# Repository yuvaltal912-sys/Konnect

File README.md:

<div align="center">

# Konnect is MOVING!!!

</div>

> ## Konnect has moved to Konnect-EDA
>
> **This repository will be archived at midnight (US Eastern) at the end of Sunday, October 25, 2026.**
> After that it's read-only. Everything here stays readable, and the releases already published stay
> available under the AGPL-3.0, but no new issues, comments or pull requests can be added.
>
> Konnect continues as **[Konnect-EDA](https://github.com/Orchis-ai-LLC/Konnect-EDA)**, from
> Orchis.ai LLC. It's the same AI-assisted KiCad design tool, and all development continues there:
>
> - **Downloads:** the [Konnect-EDA Releases page](https://github.com/Orchis-ai-LLC/Konnect-EDA/releases);
>   the first release is coming soon. Konnect-EDA is commercial, closed-source software, **free to use
>   during the beta** (until version 1.0).
> - **Bugs and feature requests:** the
>   [Konnect-EDA issue tracker](https://github.com/Orchis-ai-LLC/Konnect-EDA/issues).
> - **Want to help build it?** Sign up to contribute at
>   **[orchis.ai/konnect/join](https://orchis.ai/konnect/join)**.
> - **Contributed to Konnect?** Please answer your sign-off email, or sign in with GitHub at
>   [orchis.ai/konnect/sign-off](https://orchis.ai/konnect/sign-off). It's open until November 20.
>
> Thank you to everyone who built Konnect with us.

> **Status: beta.** The core toolchain is tested and working, but this is a young
> release and it wants real-world mileage and review. Issues and PRs are welcome —
> see [CONTRIBUTING.md](CONTRIBUTING.md) and the
> [naming conventions](docs/NAMING_CONVENTIONS.md).

> ## Add realtime research to KiCAD MCP and Konnect. Introducing Nimrod
>
> [**Nimrod**](https://nimrod.orchis.ai) is our web-research MCP server:
> quality-scored Google search, clean webpage extraction, and deep multi-source
> research. Design the board with Konnect while Nimrod pulls live parts availability, datasheets,
> and errata — no more guessing from year-old training data
>
> - Works with claude.ai, Claude Desktop, Claude Code, VS Code, and any MCP client
> - 1 credit = 1 search · extraction always free · free 50-credit trial, no card
> - Official MCP Registry: [`ai.orchis/nimrod`](https://registry.modelcontextprotocol.io)

**AI-assisted PCB design for KiCAD 10.** Konnect is a native KiCAD plugin — a single
Rust binary — that lets Claude and other AI assistants design schematics and PCBs
through the [Model Context Protocol](https://modelcontextprotocol.io) (MCP).

**269 tools across 22 on-demand toolsets.** Schematic capture, PCB layout and
routing, ERC/DRC, design-review audits, JLCPCB part search, reference
circuits, and a full manufacturing export pipeline — with bundled skills and agents
that teach Claude KiCAD conventions out of the box.

## Why Konnect exists

Konnect is the successor to [KiCAD-MCP-Server](https://github.com/mixelpixx/KiCAD-MCP-Server),
a Python/TypeScript project that proved AI-driven PCB design works — and, in the
process, showed exactly where that architecture runs out of road. Konnect was built
to fix those specific problems:

**The call path was too long.** In the original server, a single tool call travels
through TypeScript, schema validation, a spawned Python subprocess, JSON over
stdin/stdout, a command router, and finally SWIG-generated C++ proxy objects before
anything touches your board. That's four language and serialization boundaries, each
with its own failure modes — subprocess lifecycle management, stdout parsing that
filters out warnings KiCAD leaks into the stream, chunked-JSON reassembly. In
Konnect, a tool call is a function call. One process, one language, no plumbing.

**The dependency surface was enormous.** Running the original means carrying Node.js
and its npm tree, Python and its pip packages, wxPython, kicad-skip, and KiCAD's
SWIG bindings — two package ecosystems plus a binding layer, every one of them a
moving target that can break an install. Konnect is a single static binary —
20–25 MB depending on platform, a ~9 MB download. There is nothing to install
alongside it and nothing to version-match.

**SWIG is a dead end.** The original's PCB backend depends on KiCAD's SWIG Python
bindings, which KiCAD is deprecating in favor of its IPC API. SWIG also carried
real operational scars: a zone-fill call that can segfault the backend, proxy-object
comparison bugs, and a fallback path that can silently swap backends mid-session.
Konnect talks to KiCAD 10 through the official IPC API (protobuf over NNG) — the
interface KiCAD is investing in — with real-time board edits that integrate with
KiCAD's own undo/redo.

**Schematic edits should not corrupt files.** Konnect edits `.kicad_sch` files
through its own S-expression engine with atomic writes (write, fsync, rename), UUID
preservation, and round-trip tests — no third-party schematic library with known
gaps, no text-manipulation workarounds.

**Context economy is a feature.** Exposing all 269 tools to an LLM costs roughly 23K
tokens of context on every listing. Konnect's router loads a starter kit (~2K
tokens) and lets the model pull in toolsets on demand — plus built-in observability
(`get_recent_calls`, `server_stats`, JSONL call logs) so the model can diagnose its
own tool failures.

The result is smaller, faster to install, aligned with where KiCAD is going, and
built for production use rather than experimentation. The original project remains
open, maintained, and useful — see [the comparison below](#relationship-to-kicad-mcp-server).

## What it does

Instead of describing changes and applying them by hand, the AI works your project
directly:

- **Place and wire schematic components** — add resistors, ICs, connectors; wire them
  together by pin name
- **Lay out the PCB** — place, move, rotate, and route footprints in real time via
  KiCAD's IPC API, with full undo/redo integration
- **Run design checks** — ERC, DRC, connectivity validation, decoupling audits,
  power-rail review, BOM health checks
- **Export production files** — Gerbers, drill, BOM, pick-and-place, 3D models, PDF
- **Search JLCPCB parts** — find in-stock components in a local 2.5M-part catalog and
  suggest alternatives
- **Start from reference circuits** — USB-C, LDO, buck converter, STM32, I2C, LED
  templates with verified component values
- **Watch it happen** — a live schematic viewer auto-refreshes as the AI edits

The full tool catalog is documented in [tool-directory.md](tool-directory.md).

## How it works

| Layer | Mechanism |
|-------|-----------|
| Schematic editing | Direct `.kicad_sch` S-expression editing with atomic writes (no KiCAD required) |
| PCB editing | KiCad 10 IPC API (NNG + protobuf) — real-time and undo-aware; single-footprint placement has a safe headless fallback |
| Specctra routing | Revision-bound Rust DSN export, local Freerouting MCP routing, and strict one-transaction SES import; an authenticated KiCad 10 native-export bridge is explicit opt-in |
| Exports & checks | `kicad-cli` subprocess (Gerber, PDF, ERC, DRC, …) |
| Transport | MCP JSON-RPC over stdio (default), or Streamable HTTP (`transport = "http"` / `"both"`) |

Explore the request path and safety boundaries in the
[interactive architecture diagrams](docs/ARCHITECTURE_DIAGRAMS.md). They are
published from a standalone documentation repository and add no dependencies to
Konnect.

## Installation

### From the KiCAD Plugin Manager (recommended)

1. Download the package for your OS from [Releases](https://github.com/mixelpixx/Konnect/releases):
   `konnect-pcm-v<version>-windows.zip`, `-macos.zip`, or `-linux.zip`. Each
   bundles that platform's server binary — the macOS package is a universal
   build, so one download covers Apple Silicon and Intel. (The `konnect-pcm-*`
   assets are the KiCAD plugin packages; the other archives are standalone
   server binaries.)
2. Open KiCAD 10 → **Plugin and Content Manager**
3. Click **Install from File** and select the zip
4. Restart KiCAD

Verify: open the **PCB Editor** → **Tools → External Plugins** → you should see
**Konnect**.

For KiCad 10, the Konnect settings dialog also offers an optional **native
Specctra bridge**. When enabled, `export_specctra_dsn` can ask the active PCB
Editor to generate its native DSN while Konnect still binds the export to the
exact IPC snapshot and creates the strict reverse manifest used during SES
import. The bridge is local-only, authenticated, disabled by default, and not
the KiCad 11 integration path. Konnect uses its Rust exporter by default;
`native_bridge_mode: "prefer"` enables fallback to Rust when the bridge is
unavailable, while `"require"` refuses instead.

For end-to-end autorouting, run `check_freerouting`, then
`export_specctra_dsn` → `route_specctra_dsn` →
`plan_specctra_ses_import` / `apply_specctra_ses`. Readiness reports engine
discovery, native-MCP compatibility, and complete bridge availability
separately. The owned Java child is loopback-only and is reaped on success,
failure, timeout, or cancellation. The first supported profile preserves fixed
straight tracks and through vias; unlocked routing, arcs, zones, and unsupported
geometry are rejected before mutation.

### Build from source

```bash
# protoc is required (protobuf code generation), and cmake (the nng crate
# compiles the NNG C library with it).
# Windows: choco install protoc cmake
# macOS:   brew install protobuf cmake
# Linux:   apt install protobuf-compiler cmake
cargo build --release -p konnect
```

### Install guidance for your AI client

Konnect bundles shared KiCad skills for Claude and Codex. Select the client when
installing, checking, or removing that guidance:

```bash
# Existing behavior remains the default: Claude skills, agents, and hooks
konnect init

# Codex installs only the shared skills under ~/.agents/skills
konnect init --client codex
konnect status --client codex
konnect uninstall --client codex
```

MCP server startup never installs or restores guidance. Run `konnect init`
explicitly when you want those files installed; after `konnect uninstall`,
starting the server leaves them removed.

Guidance written by an older `konnect init` is not updated by upgrading the
binary. `konnect status` compares every installed skill, agent, and hook with
the bundle in the binary you run and marks each `current`, `different`, or
`missing`. The server makes the same check once for each installed version:
the first start after `konnect init` compares the files, records
the result in `~/.konnect`, and adds a one-line notice to its `initialize`
instructions if guidance is out of sync. Later starts reuse that record, so
guidance you chose to keep is not reported again. `get_installation_info`
shows the result. Re-run `konnect init` to update it.
It overwrites differing files, so keep a copy of any file you edited. `--client` remains accepted in server
commands for compatibility. For example, register a standalone binary with the
Codex CLI using:

```bash
codex mcp add konnect -- /path/to/konnect --client codex
```

Claude remains the default when `--client` is omitted. The installer tracks the
two clients independently, and a Codex install does not create or modify
`~/.claude`.

`--help` on any subcommand prints that subcommand's usage and writes nothing —
`konnect init --help` describes the installer rather than running it. An
argument Konnect does not recognise is an error rather than being ignored, so a
typo such as `--cleint codex` stops instead of quietly installing for the
default client.

To verify which Konnect process an MCP client is actually using, call the
always-visible `get_installation_info` tool. It reports the serving build,
executable path, verified installation source when one can be proven, KiCad
CLI and IPC detection, and restart guidance. A missing build commit or an
`unknown` installation source means the available evidence was insufficient;
it is not silently guessed from a directory name.

### macOS

The [Releases](https://github.com/mixelpixx/Konnect/releases) page ships
standalone server binaries for both Apple Silicon (`aarch64-apple-darwin`) and
Intel (`x86_64-apple-darwin`). They are not yet code-signed, so if you download
one through a browser, clear the quarantine flag before first launch:

```bash
tar xzf konnect-v*-aarch64-apple-darwin.tar.gz
xattr -d com.apple.quarantine ./konnect   # only needed for browser downloads
./konnect --help
```

Or build from source as above (verified on Apple Silicon; the same
`target/release/konnect` binary is the MCP server).

KiCad on macOS keeps its tools inside the app bundle and they are not on
`PATH`, so point Konnect at them in `~/Library/Application Support/konnect/config.toml`:

```toml
kicad_cli = "/Applications/KiCad/KiCad.app/Contents/MacOS/kicad-cli"
kicad_binary = "/Applications/KiCad/KiCad.app/Contents/MacOS/kicad"
# KiCad 10's IPC socket on macOS (enable it in KiCad:
# Preferences → Plugins → "Enable KiCad API")
ipc_address = "ipc:///tmp/kicad/api.sock"
```

Claude Desktop's config lives at
`~/Library/Application Support/Claude/claude_desktop_config.json`:

```json
{
  "mcpServers": {
    "konnect": {
      "command": "/path/to/konnect"
    }
  }
}
```

For Claude Code, put the same snippet in a `.mcp.json` in your project root.

The macOS PCM package (`konnect-pcm-v<version>-macos.zip`) bundles a universal
server binary, so one download covers Apple Silicon and Intel. The schematic
viewer compiles and launches on macOS (Tauri 2 uses the system WKWebView —
WebView2 is only a Windows requirement) but hasn't had the same mileage as
the Windows build yet.

## Setup with Claude Desktop

After a PCM install, the server binary lives in your KiCAD documents folder:

```
C:\Users\<YOU>\Documents\KiCad\10.0\3rdparty\plugins\com_github_mixelpixx_konnect\bin\konnect.exe
```

Edit `%APPDATA%\Claude\claude_desktop_config.json`:

```json
{
  "mcpServers": {
    "konnect": {
      "command": "C:\\Users\\<YOU>\\Documents\\KiCad\\10.0\\3rdparty\\plugins\\com_github_mixelpixx_konnect\\bin\\konnect.exe"
    }
  }
}
```

Restart Claude Desktop and the Konnect tools appear. For Claude Code, drop the same
snippet into a `.mcp.json` in your project root (see [examples/](examples/)).

## Schematic viewer

A standalone viewer that auto-refreshes as the schematic file changes:

```bash
schematic-viewer.exe path\to\your\root_schematic.kicad_sch
```

Point it at the root sheet of a hierarchical design and every sub-sheet is rendered
too, with a depth-indented sheet selector in the toolbar. Edits saved from KiCAD (or
made by the AI through the schematic tools) re-render only the sheets that changed
and refresh the view live — rendering runs against temp-folder snapshots, so the
viewer never blocks KiCAD from saving. Pan with click-drag, zoom with the wheel,
`0` to fit, `R` to refresh, drag-and-drop to open a different file. Also launchable
by the AI via the `open_schematic_viewer` tool.

Needs the WebView2 runtime (pre-installed on Windows 10/11) and a KiCAD install for
`kicad-cli` (auto-discovered, or pass `--kicad-cli <path>`). Built separately from
the main workspace — see [DEV.md](DEV.md) for build steps.

## Requirements

- KiCAD 10 (Windows is the most-tested platform; macOS works from the release
  binaries or a source build — see the [macOS section](#macos) above. Linux
  compiles and passes tests in CI but hasn't had per-platform QA yet; both are
  tracked on the [roadmap](ROADMAP.md))
- `kicad-cli` (ships with KiCAD — used for exports, ERC, DRC)
- For most PCB tools: KiCAD running with the target board open (IPC API).
  `place_component`, `move_component`, `rotate_component`, and (on KiCAD
  10.0.6+) `flip_component` can safely fall back to a closed board file when
  IPC is unreachable. An older reachable KiCAD makes `flip_component` fail
  closed with `unsupported_capability`; it never edits the file underneath a
  live editor that cannot perform the native flip.

## License: free for the little guys

Konnect is licensed under the **[GNU AGPL-3.0](LICENSE)**.

If you're a hobbyist, student, freelancer, or open-source project: **use it freely,
no strings attached.** Design boards, ship them, sell them.

If you're a business: the AGPL requires that anything you build on or around Konnect —
including software provided over a network — be open-sourced under the same license.
If that doesn't work for you, **commercial licenses are available**: see
[COMMERCIAL.md](COMMERCIAL.md).

## Relationship to KiCAD-MCP-Server

The original [Python/TypeScript project](https://github.com/mixelpixx/KiCAD-MCP-Server)
remains fully open (MIT) and maintained. Konnect is where new development happens —
the architecture it proved, rebuilt for production:

| | KiCAD-MCP-Server | Konnect |
|---|---|---|
| Runtime | Node.js + Python + SWIG bindings | Single static binary (20–25 MB) |
| Tool call path | TS → subprocess → Python → SWIG C++ | Direct function call |
| PCB backend | SWIG (deprecated by KiCAD) + experimental IPC | KiCAD 10 IPC API |
| Schematic backend | kicad-skip + custom loaders | Native S-expression engine, atomic writes |
| Context cost | Router pattern | Load/unload toolsets + observability |
| Skills / agents | — | 7 skills + 2 agents bundled |
| License | MIT | AGPL-3.0 + commercial |

## Troubleshooting

**Plugin doesn't appear in KiCAD** — install via the Plugin and Content Manager (not
manual copy), then restart KiCAD.

**PCB tools return "KiCAD must be running with the board loaded"** — open KiCAD
with that board first; most PCB tools talk to the running PCB editor. Only an
unreachable KiCAD produces that message: if KiCAD is running and the tool
refuses anyway, the error is the tool's own reason for refusing.
`place_component`, `move_component`, `rotate_component`, and (on KiCAD
10.0.6+) `flip_component` can fall back to a closed board file when no KiCAD
process is reachable. An older, reachable KiCAD makes `flip_component` refuse
rather than silently editing the file underneath it.

See [docs/TROUBLESHOOTING.md](docs/TROUBLESHOOTING.md) for socket setup, tools
that don't appear after `load_toolset`, and transaction recovery.

**"kicad-cli not found"** — common install paths are auto-detected; set the path
explicitly in the plugin settings dialog, in a `settings.json` beside the binary,
or in a `konnect.toml` in the working directory. (A file under any other name
works only when passed with `--config`.)

## Support

- Community Discord: [join the Konnect community](https://discord.gg/NVp9RGMmDu)
  for installation help, AI-client setup, design-workflow discussion,
  contributor coordination, and live project-status updates
- Issues & feature requests: [GitHub Issues](https://github.com/mixelpixx/Konnect/issues)
- Roadmap: [ROADMAP.md](ROADMAP.md)
- Contributing: [CONTRIBUTING.md](CONTRIBUTING.md)

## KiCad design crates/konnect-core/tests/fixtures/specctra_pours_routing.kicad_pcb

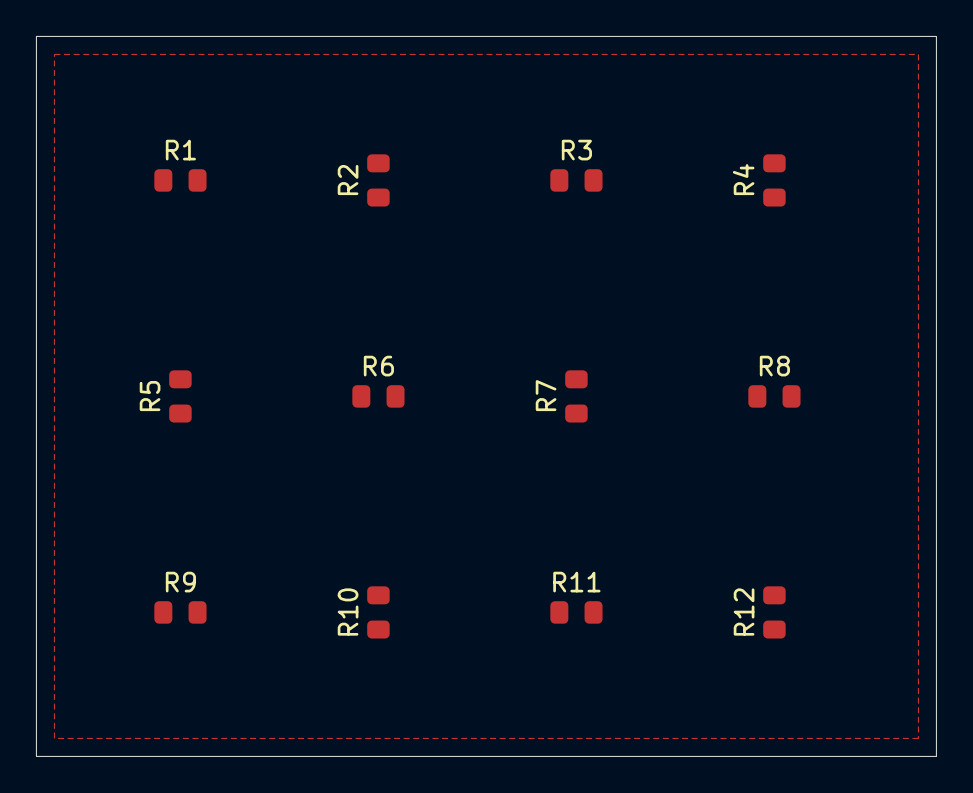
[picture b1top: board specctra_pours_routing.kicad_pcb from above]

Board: 2 copper layers, 50.0 x 40.0 mm, 12 parts (0 on the bottom side), 7 nets, no tracks yet.

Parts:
R1, R2, R3, R4, R5, R6, R7, R8, R9, R10, R11, R12: 10k; R_0805_2012Metric

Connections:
GND: R1.2, R2.2, R3.2, R4.2, R5.2, R6.2, R7.2, R8.2, R9.2, R10.2, R11.2, R12.2
S1: R1.1, R12.1
S2: R2.1, R11.1
S3: R3.1, R10.1
S4: R4.1, R9.1
S5: R5.1, R8.1
S6: R6.1, R7.1

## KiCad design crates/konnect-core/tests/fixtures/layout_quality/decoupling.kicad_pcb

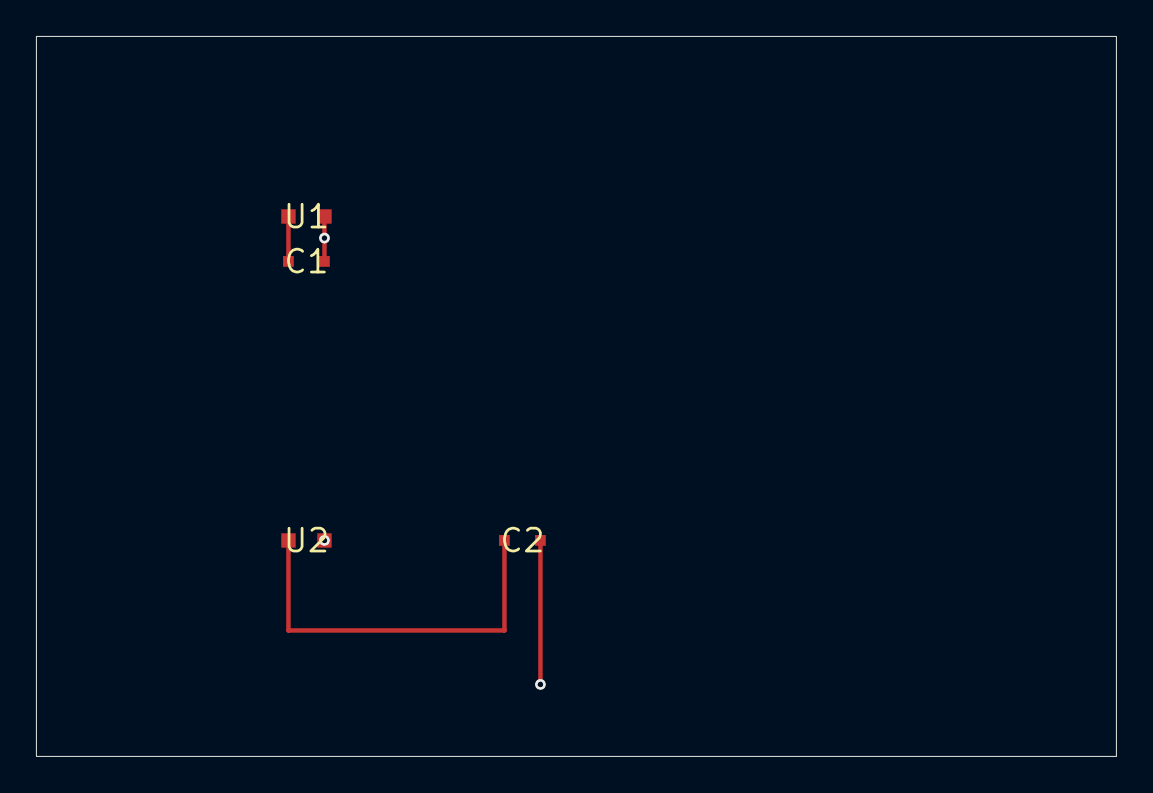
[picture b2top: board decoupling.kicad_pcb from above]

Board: 4 copper layers, 60.0 x 40.0 mm, 4 parts (0 on the bottom side), 3 nets.

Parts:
C1: C1
C2: C2
U1: U1
U2: U2

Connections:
3V3: C1.1, U1.1 (VDD)
3V3_B: C2.1, U2.1 (VDD)
GND: C1.2, C2.2, U1.2 (GND), U2.2 (GND)

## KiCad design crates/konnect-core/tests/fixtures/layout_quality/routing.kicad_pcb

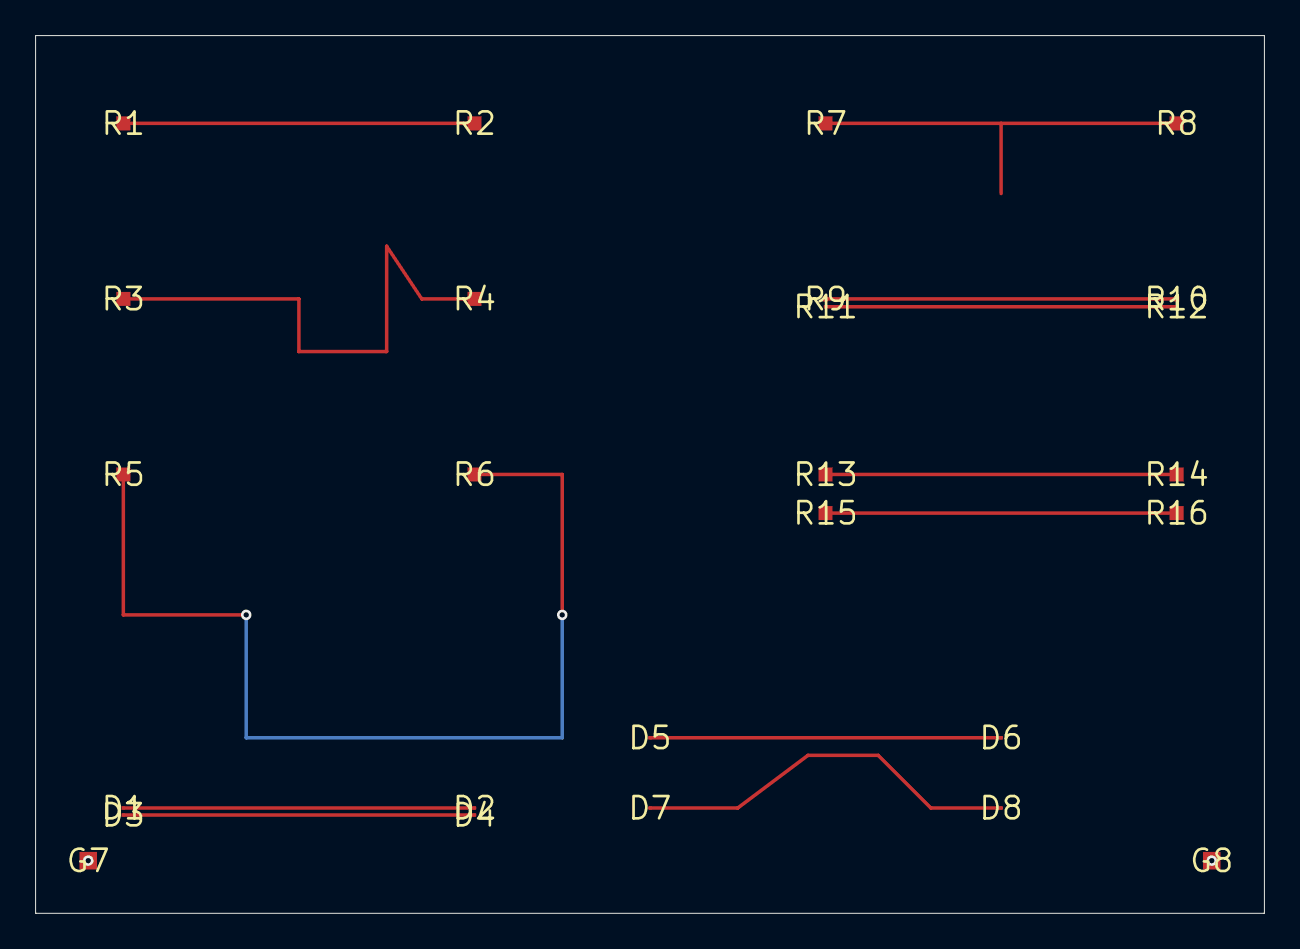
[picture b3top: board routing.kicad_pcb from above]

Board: 2 copper layers, 70.0 x 50.0 mm, 26 parts (0 on the bottom side), 13 nets.

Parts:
D1: D1
D2: D2
D3: D3
D4: D4
D5: D5
D6: D6
D7: D7
D8: D8
G7: G7
G8: G8
R1: R1
R2: R2
R3: R3
R4: R4
R5: R5
R6: R6
R7: R7
R8: R8
R9: R9
R10: R10
R11: R11
R12: R12
R13: R13
R14: R14
R15: R15
R16: R16

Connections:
DB_N: D7.1, D8.1
DB_P: D5.1, D6.1
DG_N: D3.1, D4.1
DG_P: D1.1, D2.1
GND: G7.1, G8.1
N_CLEAN: R1.1, R2.1
N_CORNER: R3.1, R4.1
N_DETOUR: R5.1, R6.1
N_PAR_A: R9.1, R10.1
N_PAR_B: R11.1, R12.1
N_SP_A: R13.1, R14.1
N_SP_B: R15.1, R16.1
N_STUB: R7.1, R8.1

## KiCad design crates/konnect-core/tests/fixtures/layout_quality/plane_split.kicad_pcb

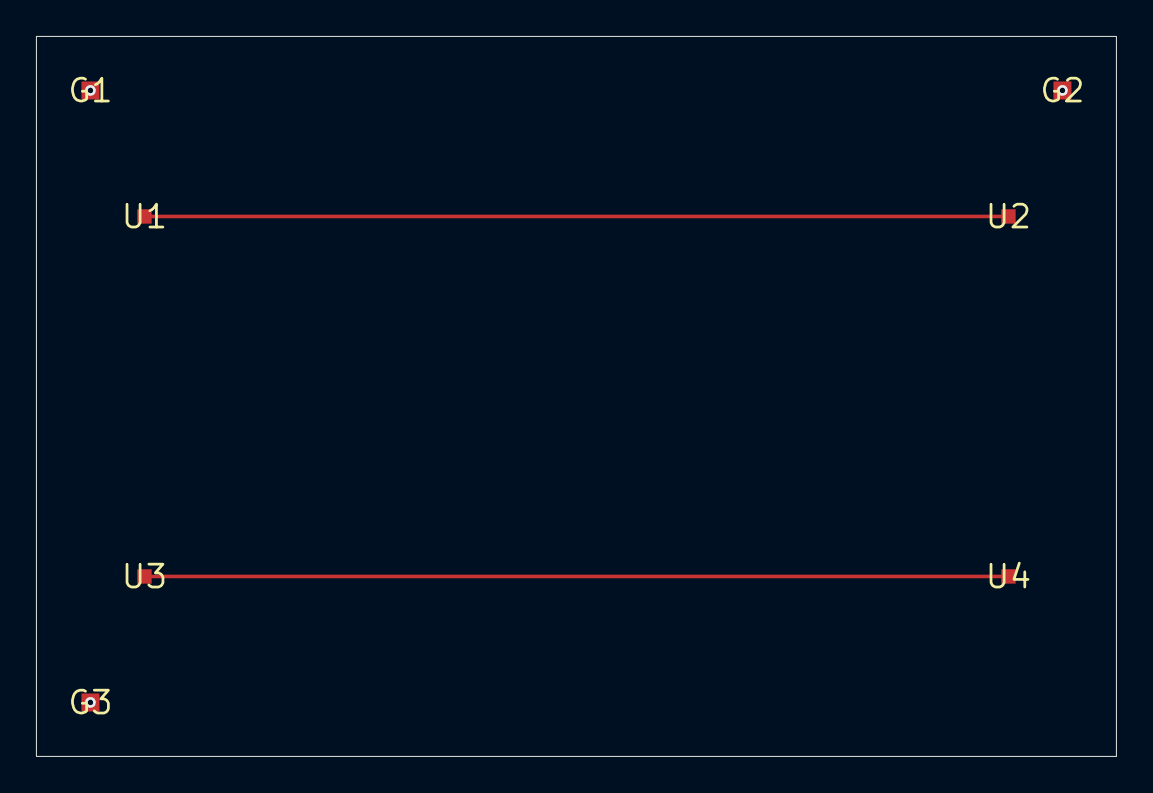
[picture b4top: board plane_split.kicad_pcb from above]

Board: 4 copper layers, 60.0 x 40.0 mm, 7 parts (0 on the bottom side), 3 nets.

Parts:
G1: G1
G2: G2
G3: G3
U1: U1
U2: U2
U3: U3
U4: U4

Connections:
CLK_OK: U1.1, U2.1
CLK_SPLIT: U3.1, U4.1
GND: G1.1, G2.1, G3.1

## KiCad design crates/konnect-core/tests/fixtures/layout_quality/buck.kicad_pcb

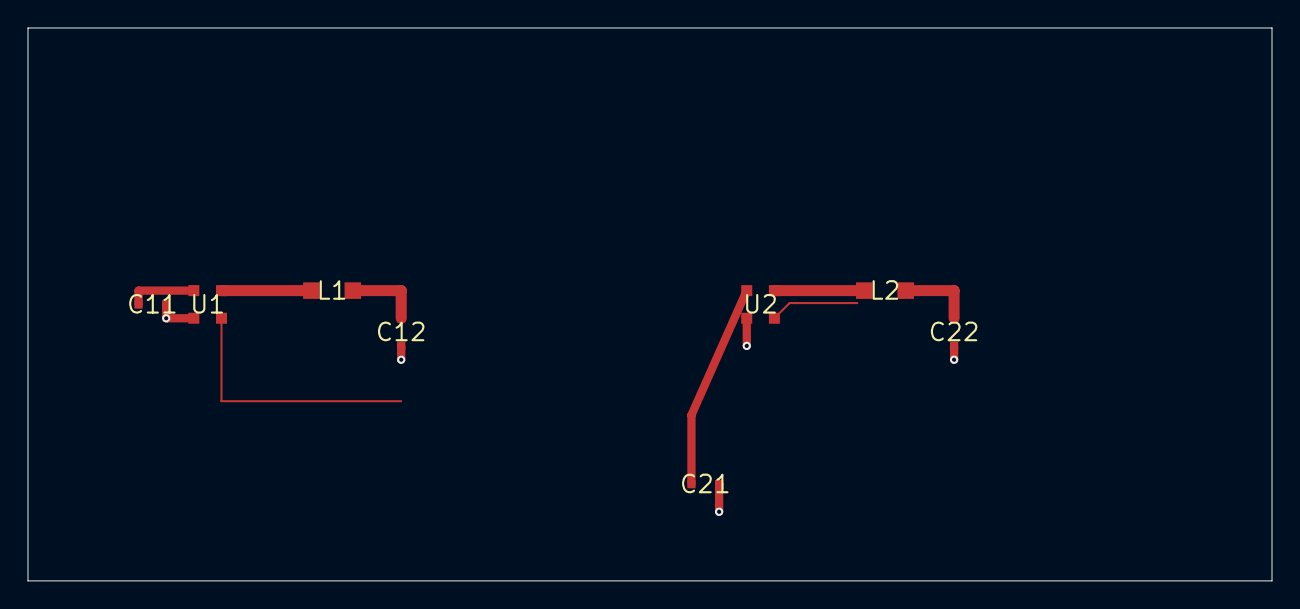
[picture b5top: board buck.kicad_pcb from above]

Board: 4 copper layers, 90.0 x 40.0 mm, 8 parts (0 on the bottom side), 7 nets.

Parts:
C11: C11
C12: C12
C21: C21
C22: C22
L1: L1
L2: L2
U1: U1
U2: U2

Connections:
GND: C11.2, C12.2, C21.2, C22.2, U1.3 (PGND), U2.3 (PGND)
SW1: L1.1, U1.2 (SW)
SW2: L2.1, U2.2 (SW)
VIN1: C11.1, U1.1 (VIN)
VIN2: C21.1, U2.1 (VIN)
VOUT1: C12.1, L1.2
VOUT2: C22.1, L2.2

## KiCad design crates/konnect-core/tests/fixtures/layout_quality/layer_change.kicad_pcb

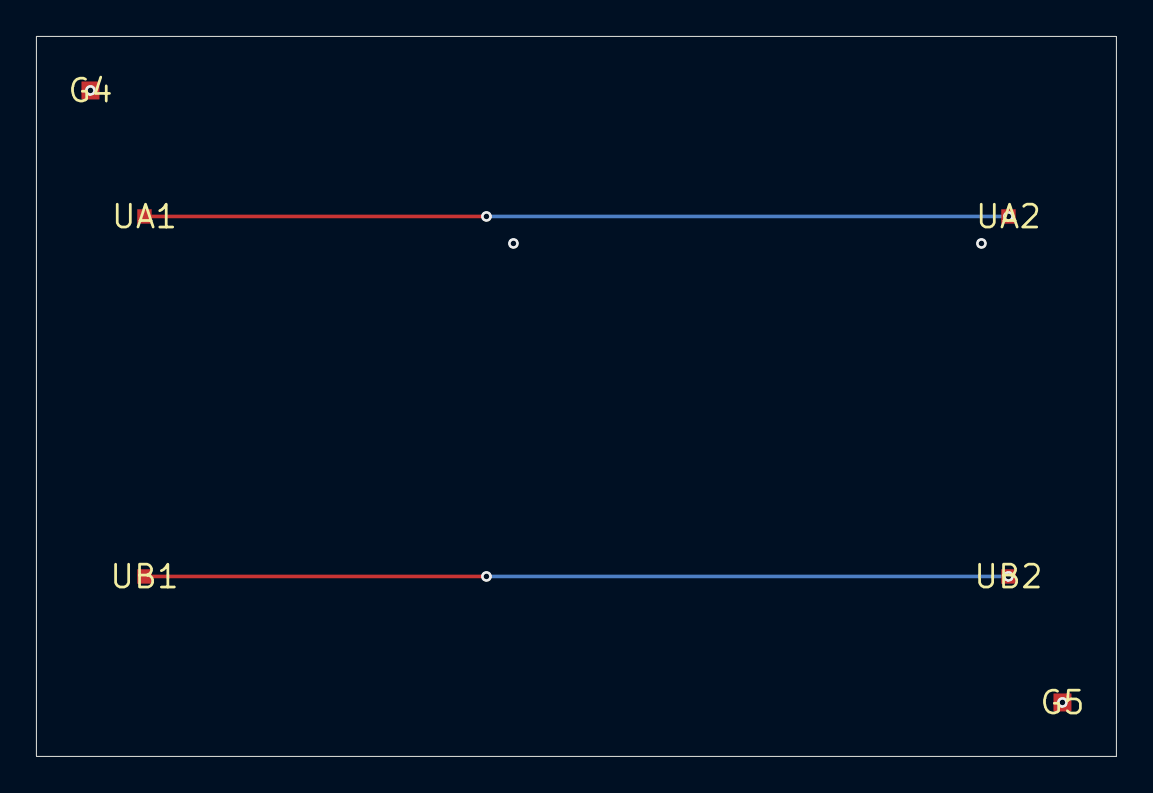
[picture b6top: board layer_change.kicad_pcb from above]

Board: 4 copper layers, 60.0 x 40.0 mm, 6 parts (0 on the bottom side), 3 nets.

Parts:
G4: G4
G5: G5
UA1: UA1
UA2: UA2
UB1: UB1
UB2: UB2

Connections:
CLK_BARE: UB1.1, UB2.1
CLK_STITCHED: UA1.1, UA2.1
GND: G4.1, G5.1

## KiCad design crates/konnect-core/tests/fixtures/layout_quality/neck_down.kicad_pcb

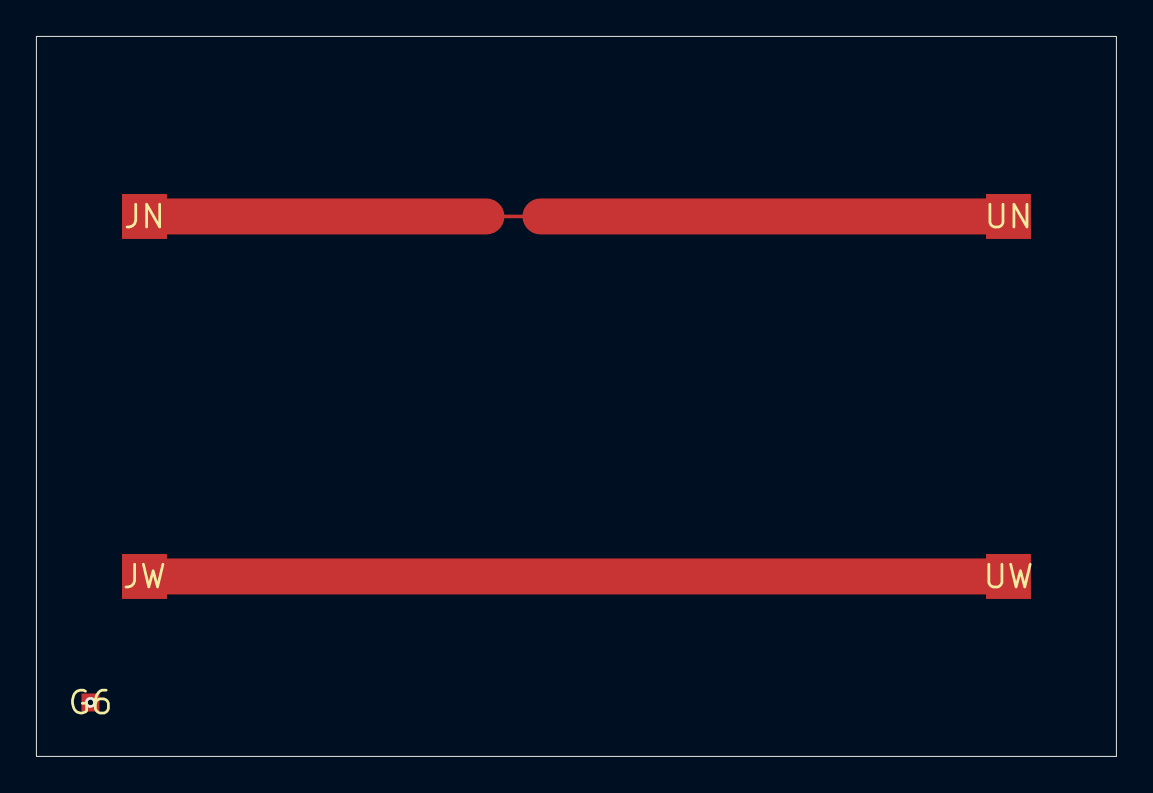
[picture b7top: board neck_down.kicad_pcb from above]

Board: 2 copper layers, 60.0 x 40.0 mm, 5 parts (0 on the bottom side), 2 nets.

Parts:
G6: G6
JN: JN
JW: JW
UN: UN
UW: UW

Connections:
P5V_NECK: JN.1, UN.1
P5V_WIDE: JW.1, UW.1

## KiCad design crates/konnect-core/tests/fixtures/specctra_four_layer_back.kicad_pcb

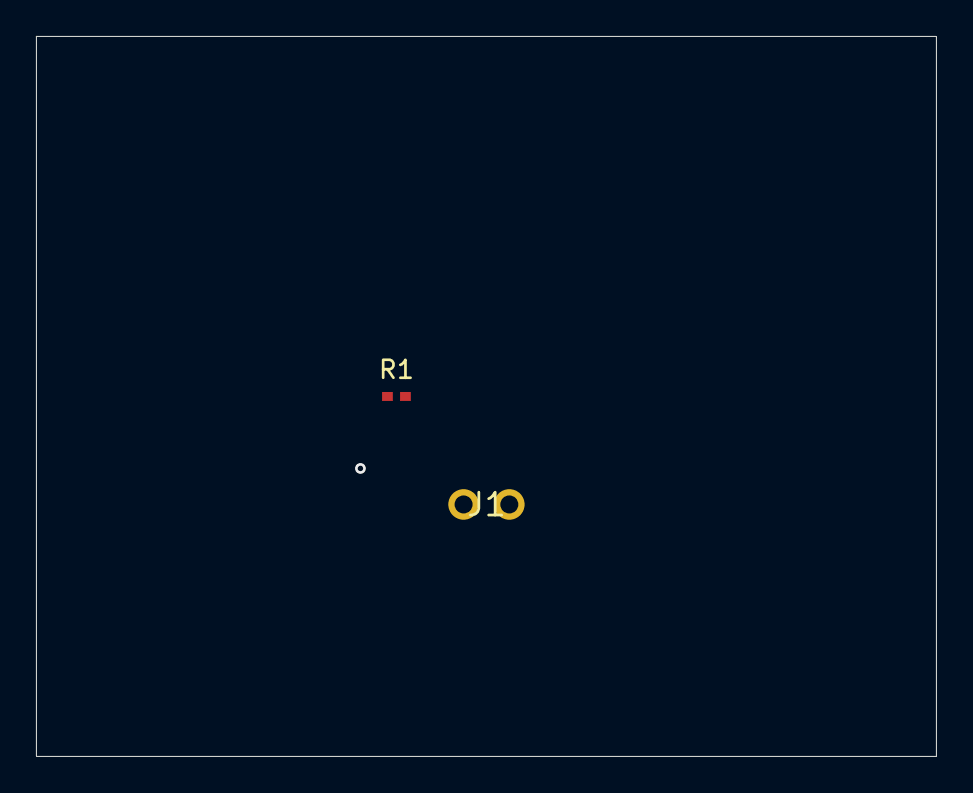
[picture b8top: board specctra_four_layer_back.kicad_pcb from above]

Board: 4 copper layers, 50.0 x 40.0 mm, 3 parts (1 on the bottom side), 2 nets.

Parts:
J1: CONN
R1: 10k; R_0402
R2: 4.7k; R_0402

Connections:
GND: J1.1, R1.2, R2.1
VCC: J1.2, R1.1, R2.2
